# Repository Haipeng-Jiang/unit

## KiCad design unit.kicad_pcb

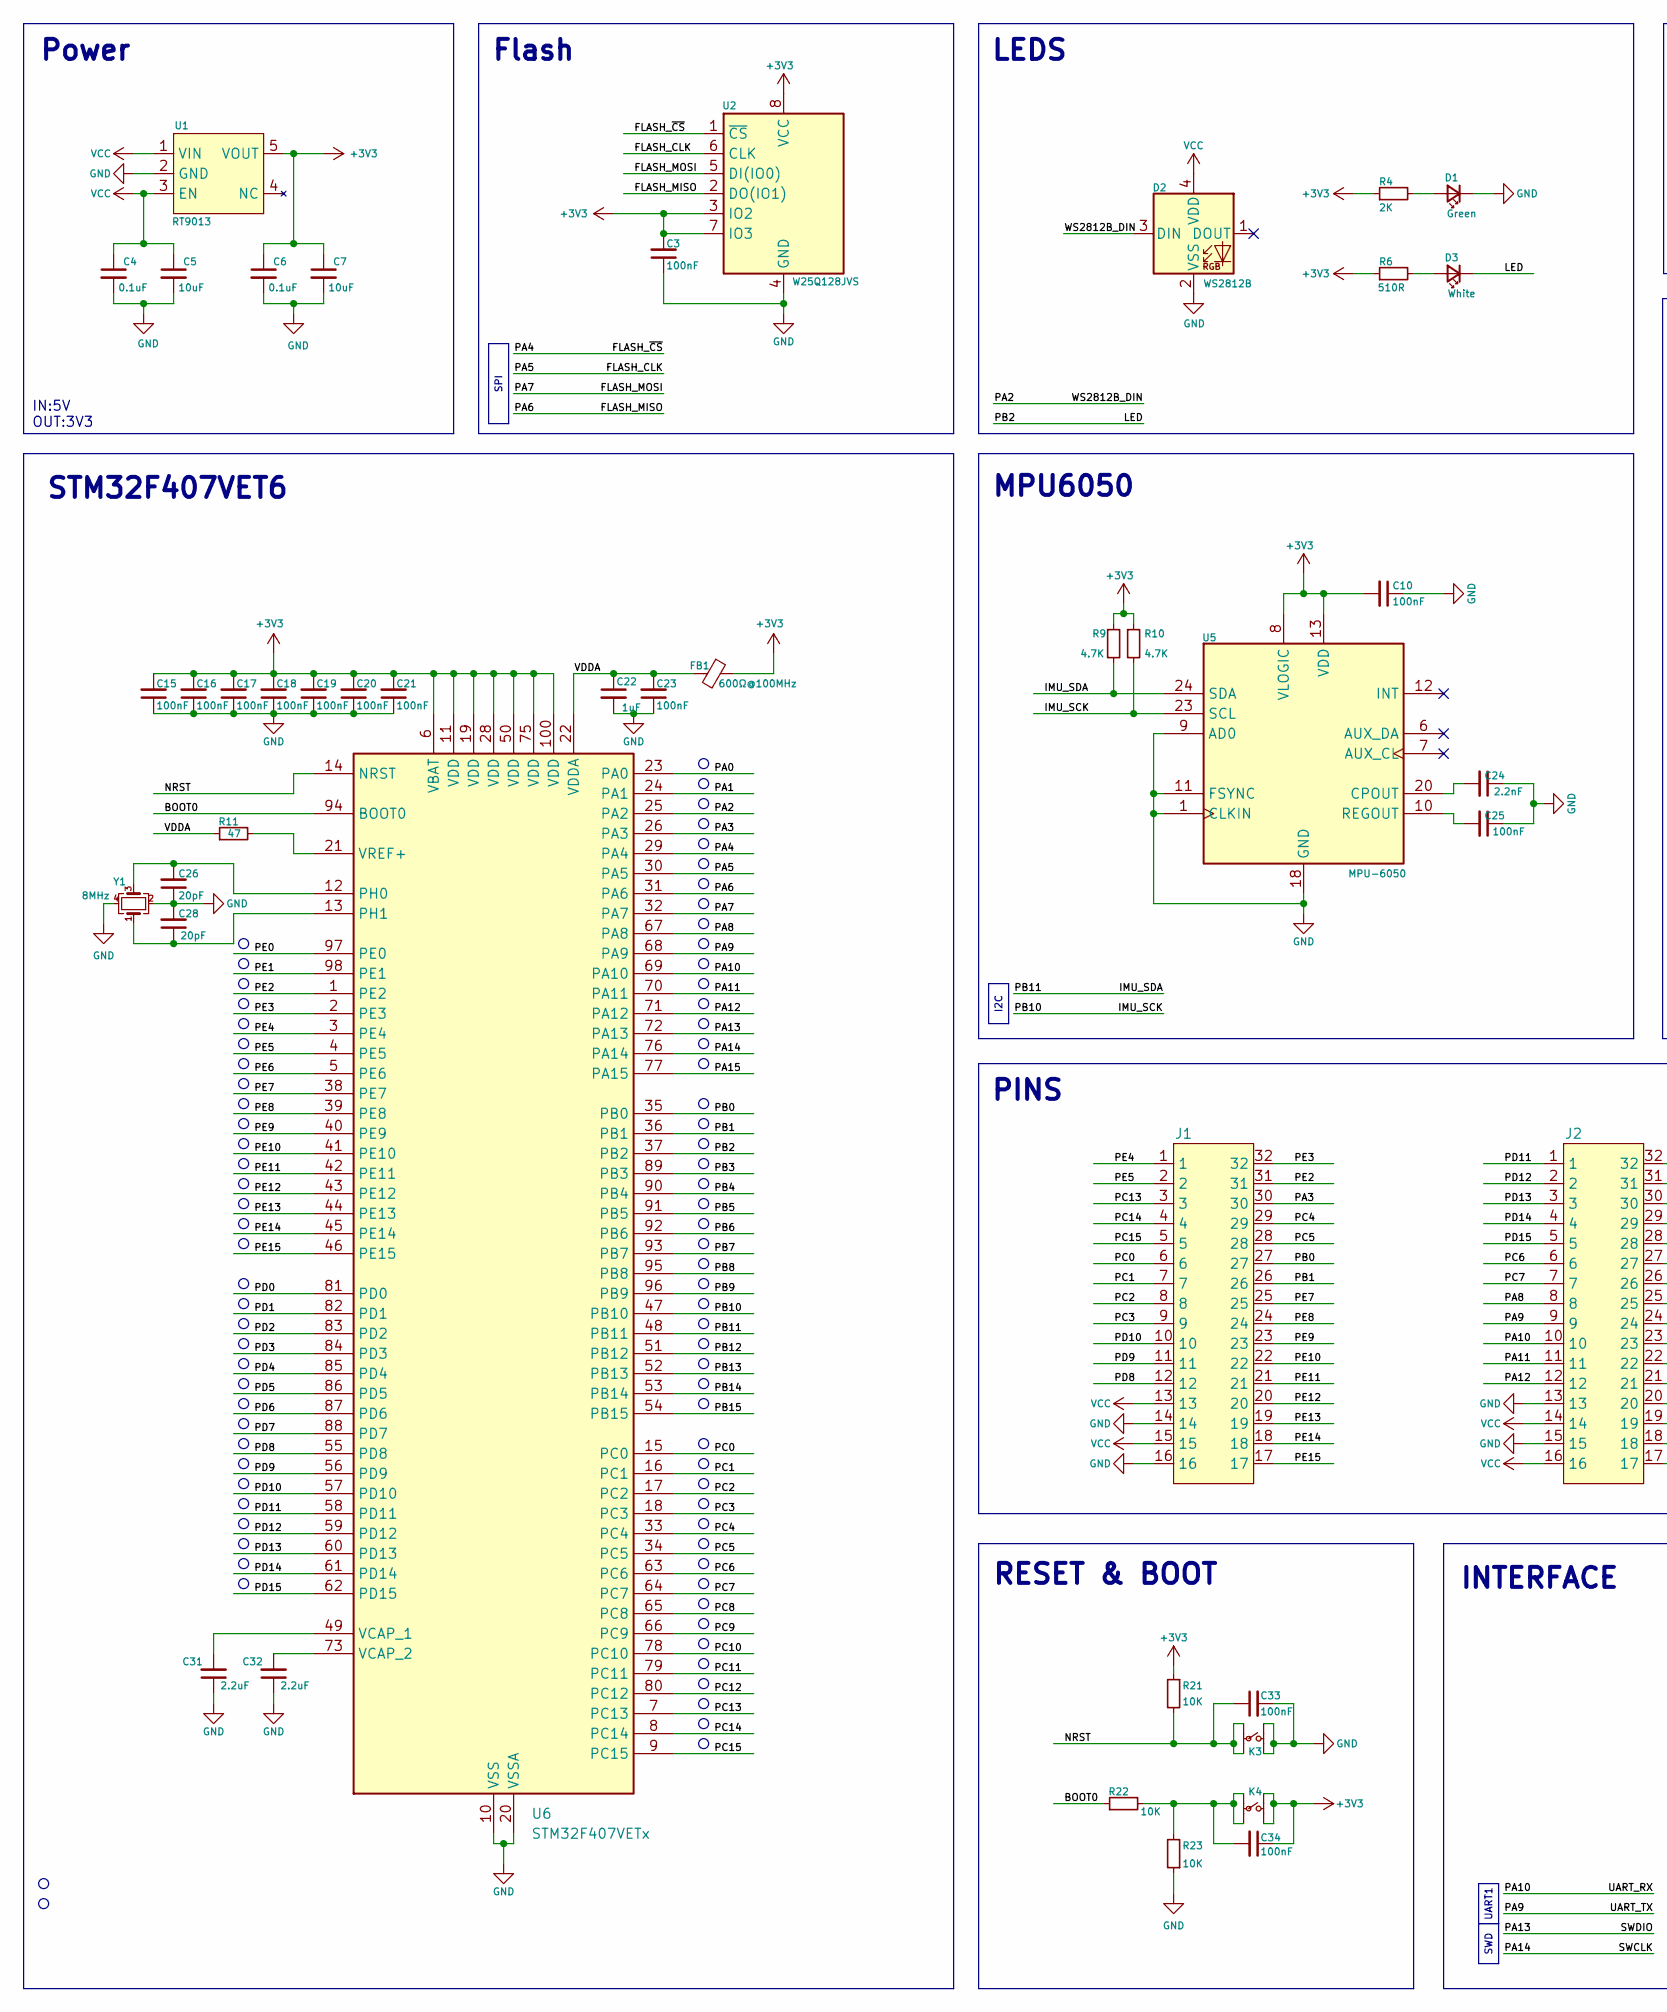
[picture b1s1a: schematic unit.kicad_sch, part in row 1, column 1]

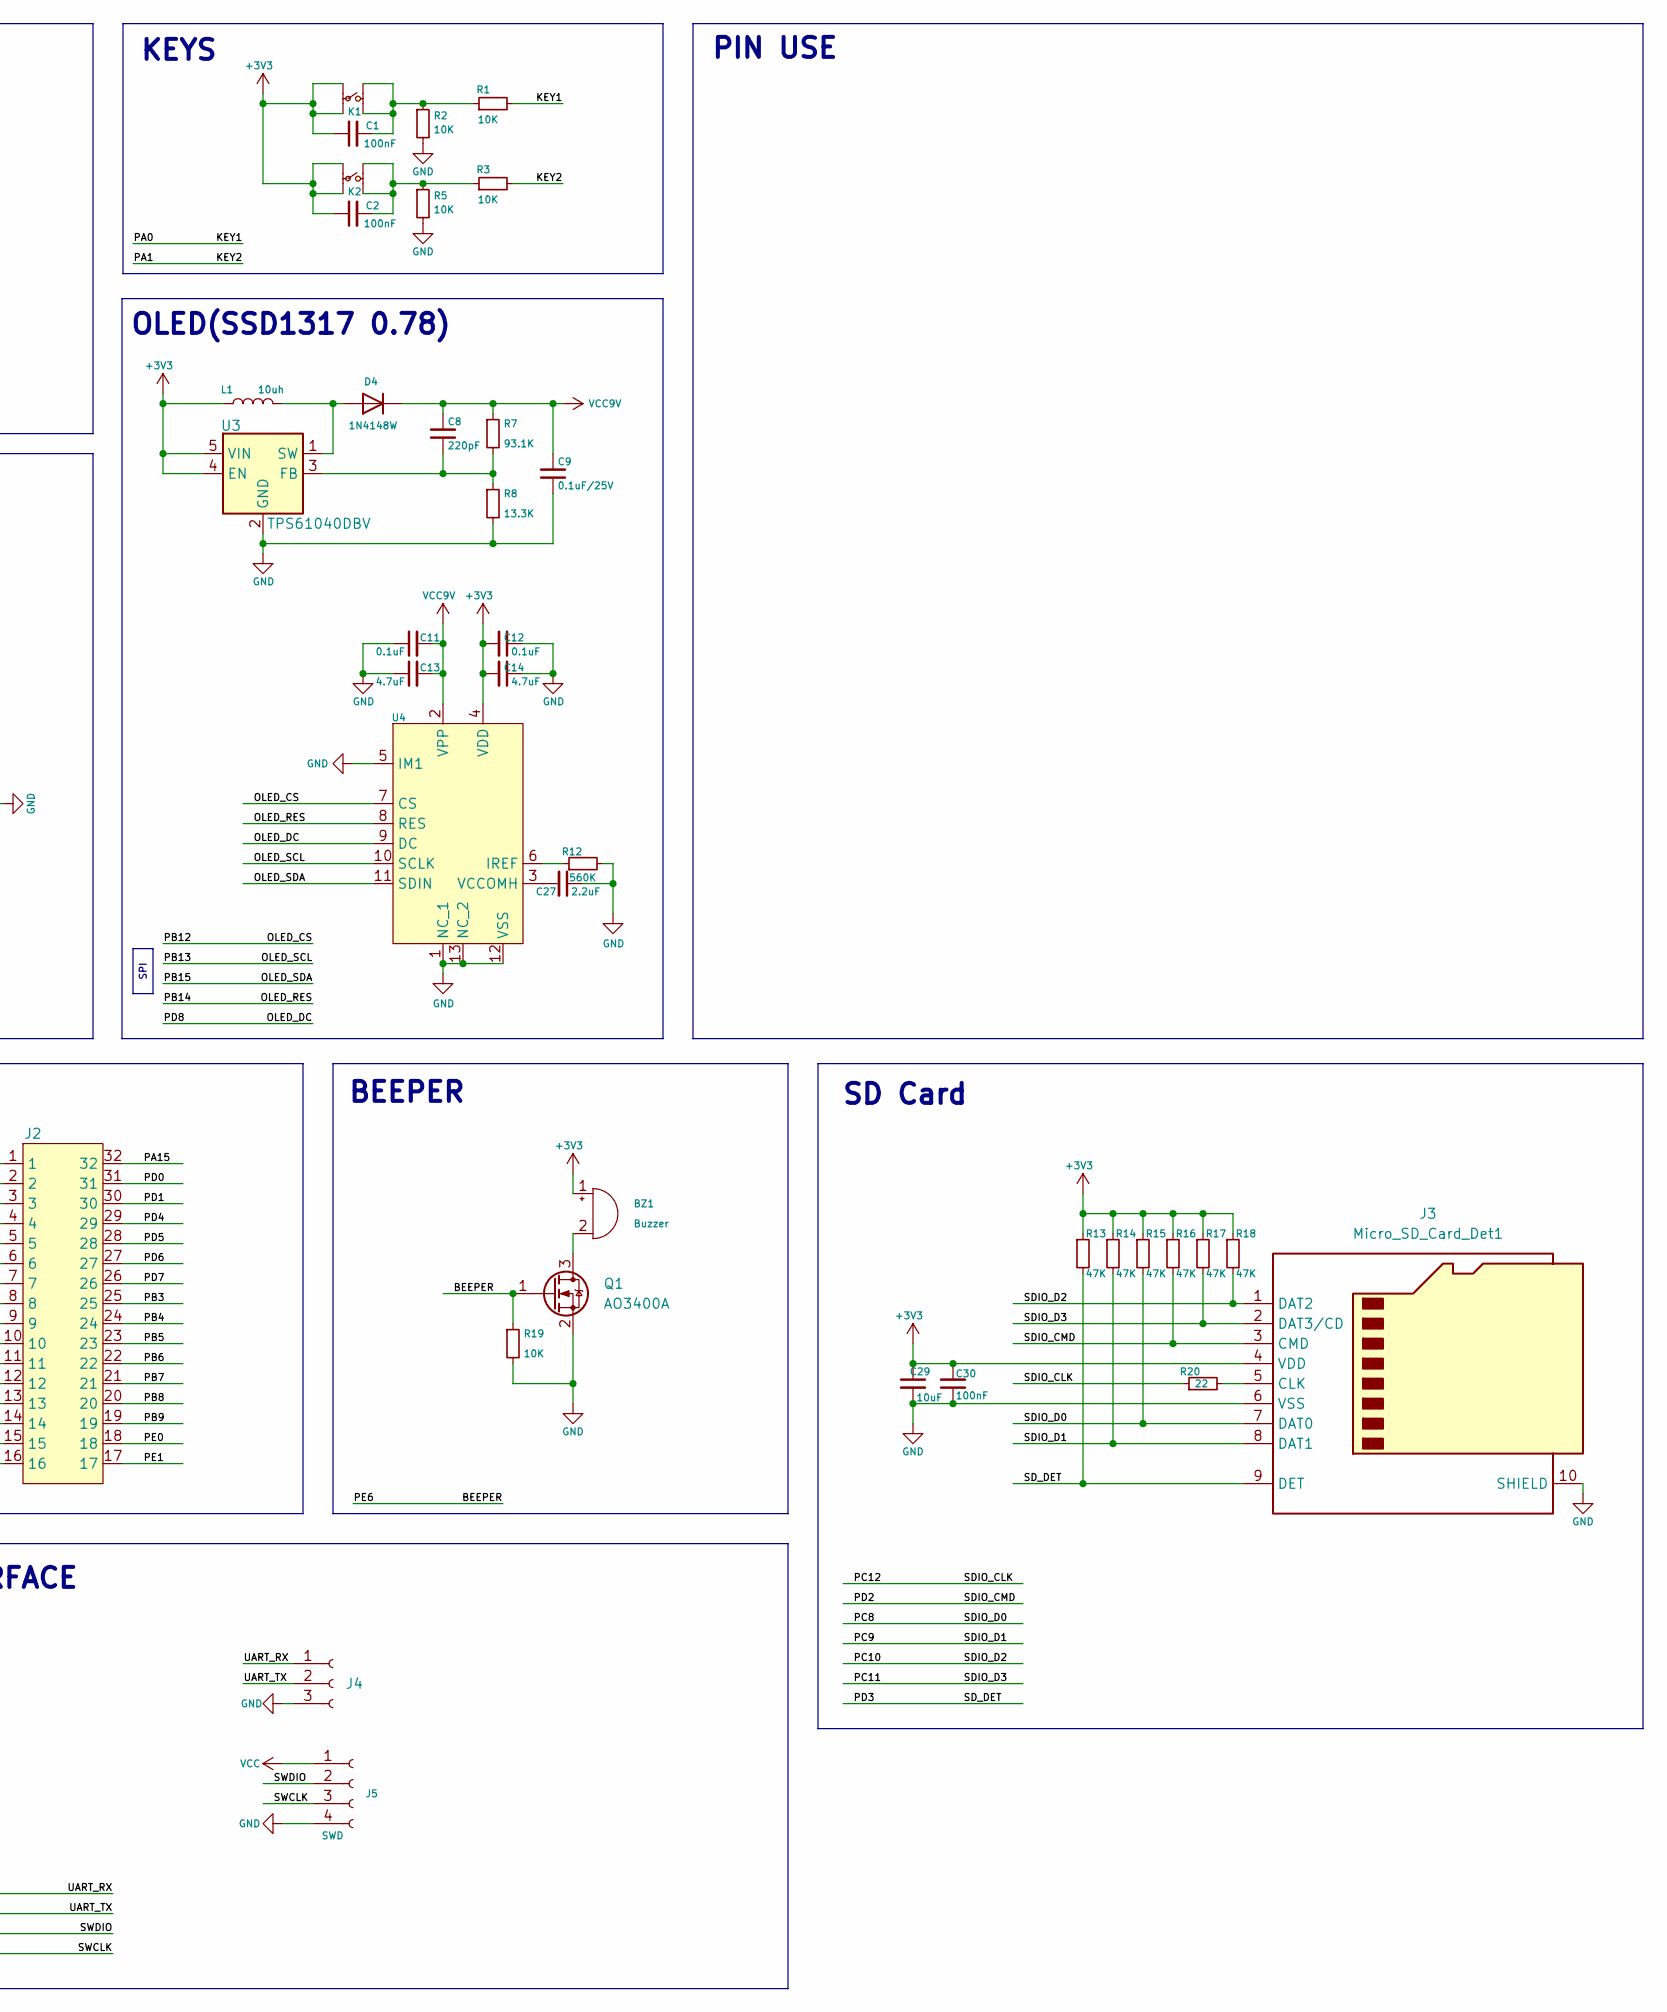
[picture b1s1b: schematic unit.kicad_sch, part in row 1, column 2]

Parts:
BZ1: Buzzer; BUZ-SMD_L5.0-W5.5-P4.60
C1, C2, C3, C10, C15, C16, C17, C18, C19, C20, C21, C23, C25, C30, C33, C34: 100nF; C_0402_1005Metric
C4, C6, C11, C12: 0.1uF; C_0402_1005Metric
C5, C7, C29: 10uF; C_0402_1005Metric
C8: 220pF; C_0402_1005Metric
C9: 0.1uF/25V; C_0402_1005Metric
C13, C14: 4.7uF; C_0402_1005Metric
C22: 1uF; C_0402_1005Metric
C24: 2.2nF; C_0402_1005Metric
C26, C28: 20pF; C_0402_1005Metric
C27, C31, C32: 2.2uF; C_0402_1005Metric
D1: Green; LED_0603_1608Metric
D2: WS2812B; LED_WS2812B-2020_PLCC4_2.0x2.0mm
D3: White; LED_0603_1608Metric
D4: 1N4148W; D_SOD-523
FB1: 600Ω@100MHz; L_0603_1608Metric
J1, J2: M_32PIN
J3: Micro_SD_Card_Det1; TF-SMD_TF-15-15
J4: Conn_01x03_Socket; CONN-SMD_3P-P1.25_JUSHUO_GH125-S03DCA-00
J5: SWD; CONN-SMD_4P-P1.27_GH125-S04DCA-00
K1, K2, K3, K4: SW-SMD_4P-L4.2-W3.3-P2.15-LS5.1
L1: 10uh; L_0603_1608Metric
Q1: AO3400A; SOT-23
R1, R2, R3, R5, R19, R21, R22, R23: 10K; R_0402_1005Metric
R4: 2K; R_0402_1005Metric
R6: 510R; R_0402_1005Metric
R7: 93.1K; R_0402_1005Metric
R8: 13.3K; R_0402_1005Metric
R9, R10: 4.7K; R_0402_1005Metric
R11: 47; R_0402_1005Metric
R12: 560K; R_0402_1005Metric
R13, R14, R15, R16, R17, R18: 47K; R_0402_1005Metric
R20: 22; R_0402_1005Metric
U1: RT9013; SOT-23-5
U2: W25Q128JVS; SOIC-8_5.23x5.23mm_P1.27mm
U3: TPS61040DBV; SOT-23-5
U4: oled_0.78_ssd1317
U5: MPU-6050; InvenSense_QFN-24_4x4mm_P0.5mm
U6: STM32F407VETx; LQFP-100_14x14mm_P0.5mm
Y1: 8MHz; Crystal_SMD_3225-4Pin_3.2x2.5mm

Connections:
+3V3: BZ1.1 (+), C1.1, C2.1, C3.2, C6.1, C7.1, C10.2, C12.2, C14.2, C15.2, C16.2, C17.2, C18.2, C19.2, C20.2, C21.2, C29.1, C30.2, C34.1, FB1.1, J3.4 (VDD), K1.3, K1.4, K2.3, K2.4, K4.1, K4.2, L1.1, R4.1, R6.1, R9.1, R10.1, R13.1, R14.1, R15.1, R16.1, R17.1, R18.1, R21.1, U1.5 (VOUT), U2.3 (IO2), U2.7 (IO3), U2.8 (VCC), U3.4 (EN), U3.5 (VIN), U4.4 (VDD), U5.8 (VLOGIC), U5.13 (VDD), U6.6 (VBAT), U6.11 (VDD), U6.19 (VDD), U6.28 (VDD), U6.50 (VDD), U6.75 (VDD), U6.100 (VDD)
/BEEPER: Q1.1 (G), R19.1, U6.5 (PE6)
/BOOT0: R22.1, U6.94 (BOOT0)
/FLASH_CLK: U2.6 (CLK), U6.30 (PA5)
/FLASH_MISO: U2.2 (DO(IO1)), U6.31 (PA6)
/FLASH_MOSI: U2.5 (DI(IO0)), U6.32 (PA7)
/FLASH_~CS: U2.1 (~CS), U6.29 (PA4)
/IMU_SCK: R10.2, U5.23 (SCL), U6.47 (PB10)
/IMU_SDA: R9.2, U5.24 (SDA), U6.48 (PB11)
/KEY1: R1.2, U6.23 (PA0)
/KEY2: R3.2, U6.24 (PA1)
/LED: D3.1 (K), U6.37 (PB2)
/NRST: C33.1, K3.3, K3.4, R21.2, U6.14 (NRST)
/OLED_CS: U4.7 (CS), U6.51 (PB12)
/OLED_DC: J1.12, U4.9 (DC), U6.55 (PD8)
/OLED_RES: U4.8 (RES), U6.53 (PB14)
/OLED_SCL: U4.10 (SCLK), U6.52 (PB13)
/OLED_SDA: U4.11 (SDIN), U6.54 (PB15)
/PA2: D2.3 (DIN), U6.25 (PA2)
/PA3: J1.30, U6.26 (PA3)
/PA8: J2.8, U6.67 (PA8)
/PA9: J2.9, J4.2, U6.68 (PA9)
/PA10: J2.10, J4.1, U6.69 (PA10)
/PA11: J2.11, U6.70 (PA11)
/PA12: J2.12, U6.71 (PA12)
/PA13: J5.2, U6.72 (PA13)
/PA14: J5.3, U6.76 (PA14)
/PA15: J2.32, U6.77 (PA15)
/PB0: J1.27, U6.35 (PB0)
/PB1: J1.26, U6.36 (PB1)
/PB3: J2.25, U6.89 (PB3)
/PB4: J2.24, U6.90 (PB4)
/PB5: J2.23, U6.91 (PB5)
/PB6: J2.22, U6.92 (PB6)
/PB7: J2.21, U6.93 (PB7)
/PB8: J2.20, U6.95 (PB8)
/PB9: J2.19, U6.96 (PB9)
/PC0: J1.6, U6.15 (PC0)
/PC1: J1.7, U6.16 (PC1)
/PC2: J1.8, U6.17 (PC2)
/PC3: J1.9, U6.18 (PC3)
/PC4: J1.29, U6.33 (PC4)
/PC5: J1.28, U6.34 (PC5)
/PC6: J2.6, U6.63 (PC6)
/PC7: J2.7, U6.64 (PC7)
/PC8: J3.7 (DAT0), R15.2, U6.65 (PC8)
/PC9: J3.8 (DAT1), R14.2, U6.66 (PC9)
/PC10: J3.1 (DAT2), R18.2, U6.78 (PC10)
/PC11: J3.2 (DAT3/CD), R17.2, U6.79 (PC11)
/PC12: R20.1, U6.80 (PC12)
/PC13: J1.3, U6.7 (PC13)
/PC14: J1.4, U6.8 (PC14)
/PC15: J1.5, U6.9 (PC15)
/PD0: J2.31, U6.81 (PD0)
/PD1: J2.30, U6.82 (PD1)
/PD2: J3.3 (CMD), R16.2, U6.83 (PD2)
/PD3: J3.9 (DET), R13.2, U6.84 (PD3)
/PD4: J2.29, U6.85 (PD4)
/PD5: J2.28, U6.86 (PD5)
/PD6: J2.27, U6.87 (PD6)
/PD7: J2.26, U6.88 (PD7)
/PD9: J1.11, U6.56 (PD9)
/PD10: J1.10, U6.57 (PD10)
/PD11: J2.1, U6.58 (PD11)
/PD12: J2.2, U6.59 (PD12)
/PD13: J2.3, U6.60 (PD13)
/PD14: J2.4, U6.61 (PD14)
/PD15: J2.5, U6.62 (PD15)
/PE0: J2.18, U6.97 (PE0)
/PE1: J2.17, U6.98 (PE1)
/PE2: J1.31, U6.1 (PE2)
/PE3: J1.32, U6.2 (PE3)
/PE4: J1.1, U6.3 (PE4)
/PE5: J1.2, U6.4 (PE5)
/PE7: J1.25, U6.38 (PE7)
/PE8: J1.24, U6.39 (PE8)
/PE9: J1.23, U6.40 (PE9)
/PE10: J1.22, U6.41 (PE10)
/PE11: J1.21, U6.42 (PE11)
/PE12: J1.20, U6.43 (PE12)
/PE13: J1.19, U6.44 (PE13)
/PE14: J1.18, U6.45 (PE14)
/PE15: J1.17, U6.46 (PE15)
/VDDA: C22.1, C23.2, FB1.2, R11.1, U6.22 (VDDA)
GND: C3.1, C4.2, C5.2, C6.2, C7.2, C9.1, C10.1, C11.1, C12.1, C13.1, C14.1, C15.1, C16.1, C17.1, C18.1, C19.1, C20.1, C21.1, C22.2, C23.1, C24.1, C25.1, C26.1, C27.1, C28.2, C29.2, C30.1, C31.1, C32.1, C33.2, D1.1 (K), D2.2 (VSS), J1.14, J1.16, J2.13, J2.15, J3.6 (VSS), J3.10 (SHIELD), J4.3, J5.4, K3.1, K3.2, Q1.2 (S), R2.2, R5.2, R8.2, R12.2, R19.2, R23.1, U1.2 (GND), U2.4 (GND), U3.2 (GND), U4.1 (NC_1), U4.5 (IM1), U4.12 (VSS), U4.13 (NC_2), U5.1 (CLKIN), U5.9 (AD0), U5.11 (FSYNC), U5.18 (GND), U6.10 (VSS), U6.20 (VSSA), U6.27 (VSS), U6.74 (VSS), U6.99 (VSS), Y1.2, Y1.4
unnamed: BZ1.2 (-), Q1.3 (D)
unnamed: C1.2, K1.1, K1.2, R1.1, R2.1
unnamed: C2.2, K2.1, K2.2, R3.1, R5.1
unnamed: C34.2, K4.3, K4.4, R22.2, R23.2
unnamed: D1.2 (A), R4.2
unnamed: D3.2 (A), R6.2
unnamed: D4.2 (A), L1.2, U3.1 (SW)
unnamed: J3.5 (CLK), R20.2
unnamed: C8.1, R7.2, R8.1, U3.3 (FB)
unnamed: R12.1, U4.6 (IREF)
unnamed: C27.2, U4.3 (VCCOMH)
unnamed: C24.2, U5.20 (CPOUT)
unnamed: C25.2, U5.10 (REGOUT)
unnamed: C26.2, U6.12 (PH0), Y1.3
unnamed: C28.1, U6.13 (PH1), Y1.1
unnamed: C31.2, U6.49 (VCAP_1)
unnamed: C32.2, U6.73 (VCAP_2)
unnamed: R11.2, U6.21 (VREF+)
VCC: C4.1, C5.1, D2.4 (VDD), J1.13, J1.15, J2.14, J2.16, J5.1, U1.1 (VIN), U1.3 (EN)
VCC9V: C8.2, C9.2, C11.2, C13.2, D4.1 (K), R7.1, U4.2 (VPP)

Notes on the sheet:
UART1
SPI
SWD
I2C
PIN USE
STM32F407VET6
MPU6050
LEDS
IN:5V OUT:3V3
Flash
SD Card
OLED(SSD1317 0.78)
PINS
BEEPER
Power
INTERFACE
KEYS
RESET & BOOT

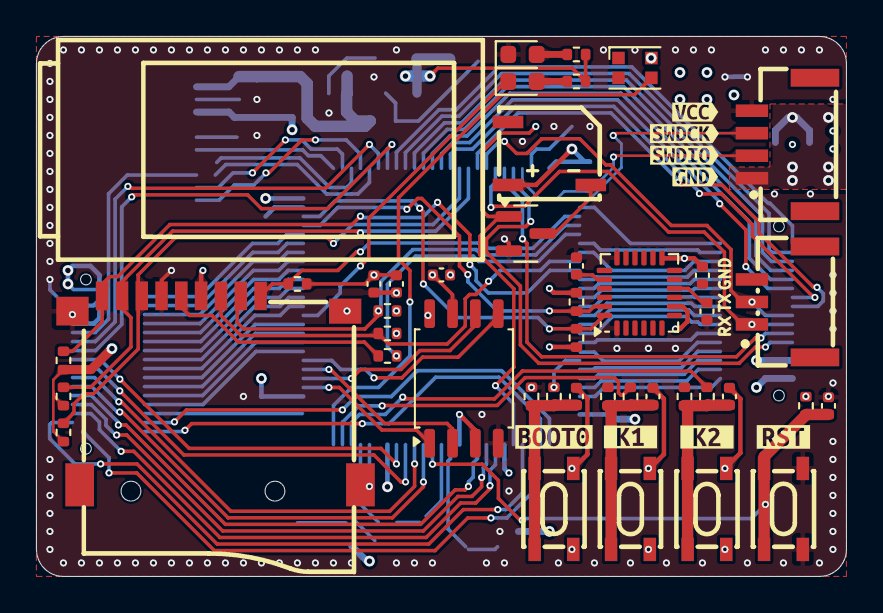
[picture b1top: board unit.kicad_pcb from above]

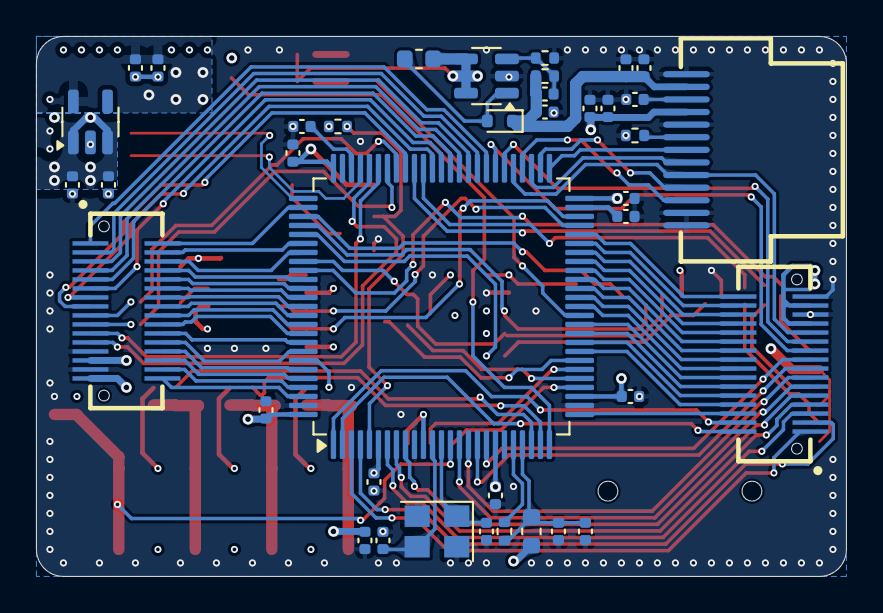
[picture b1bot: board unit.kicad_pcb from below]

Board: 4 copper layers, 45.0 x 30.0 mm, 89 parts (38 on the bottom side), 105 nets.

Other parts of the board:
kibuzzard-66CADDA5: G***; kibuzzard-66CADDA5
kibuzzard-66CADDDA: G***; kibuzzard-66CADDDA
kibuzzard-66CADE49: G***; kibuzzard-66CADE49
kibuzzard-66CADE69: G***; kibuzzard-66CADE69
kibuzzard-66CADF6D: G***; kibuzzard-66CADF6D
kibuzzard-66CADF7A: G***; kibuzzard-66CADF7A
kibuzzard-66CADF13: G***; kibuzzard-66CADF13
kibuzzard-66CADF25: G***; kibuzzard-66CADF25

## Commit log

2024-08-23 init commit
